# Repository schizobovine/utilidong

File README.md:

utilidong
=============================

Various utility dongles that have uses in many projects:

* USB-to-UART adapter based on the FTDI FT231XS
* Lithium polymer USB battery charger based on the Microchip MCP73831
* DC-to-DC SEPIC converter based on the Linear LT1610

Yes, all of these are available elsewhere for cheaper, on platforms that have had better testing, etc. Don't use them for anything you care about, really, since this is more CAD practice for myself.

Eventually will be a single unit for handling power and UART communications with a microcontroller.

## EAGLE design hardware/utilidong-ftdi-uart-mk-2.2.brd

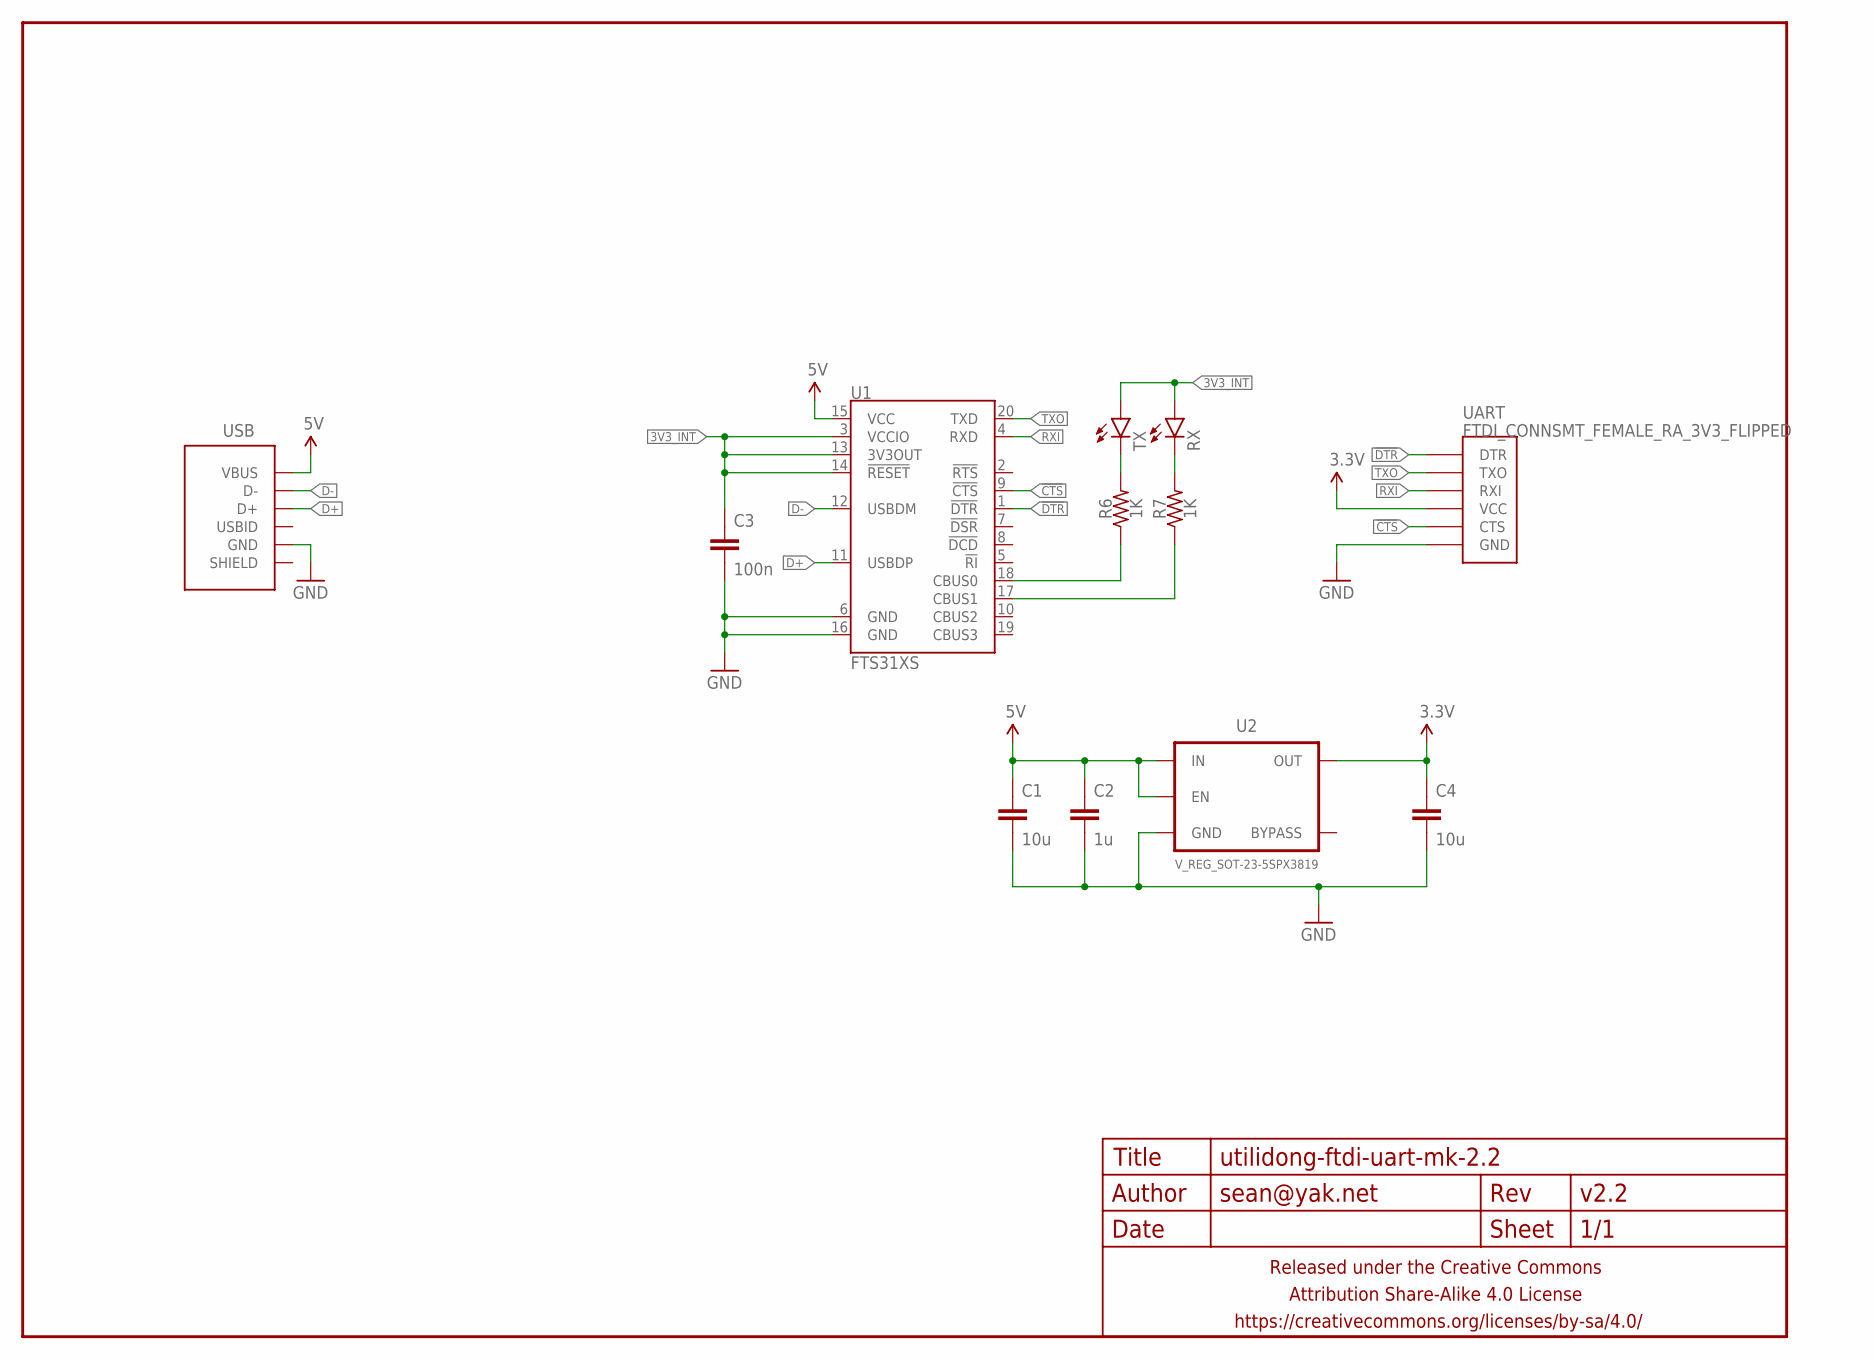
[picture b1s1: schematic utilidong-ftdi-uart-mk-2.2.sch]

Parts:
C1, C4: 10u; C0805
C2: 1u; C0603-TIGHTER
C3: 100n; C0603-TIGHTER
FRAME1: FRAME-LETTERNO_PACKAGE; DUMMY
R6, R7: 1K; R0603-TIGHTER
RX: LED0603-TIGHT; LED-0603-TIGHT
TX: LED0603-TIGHT; LED-0603-TIGHT
U1: FTS31XS; SSOP20_L
U2: V_REG_SOT-23-5SPX3819; SOT23-5
UART: FTDI_CONNSMT_FEMALE_RA_3V3_FLIPPED; FTDI_CONN_SMT_FEMALE_RA_3V3_FLIPPED
USB: USB-AB-SHIELDFCI-10103594-USB-MICRO-B-EVENLESS; FCI-101035840-USB-MICRO-B-EVENLESS

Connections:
3.3V: C4.1, U2.5 (OUT), UART.4 (VCC)
3V3_INT: C3.1, RX.A, TX.A, U1.3 (VCCIO), U1.13 (3V3OUT), U1.14 (!RESET)
5V: C1.1, C2.1, U1.15 (VCC), U2.1 (IN), U2.3 (EN), USB.1 (VBUS)
!CTS: U1.9 (!CTS), UART.5 (CTS)
!DTR: U1.1 (!DTR), UART.1 (DTR)
D+: U1.11 (USBDP), USB.3 (D+)
D-: U1.12 (USBDM), USB.2 (D-)
GND: C1.2, C2.2, C3.2, C4.2, U1.6 (GND), U1.16 (GND), U2.2 (GND), UART.6 (GND), USB.5 (GND)
unnamed: R6.1, U1.18 (CBUS0)
unnamed: R6.2, TX.C
unnamed: R7.2, RX.C
unnamed: R7.1, U1.17 (CBUS1)
RXI: U1.4 (RXD), UART.3 (RXI)
TXO: U1.20 (TXD), UART.2 (TXO)

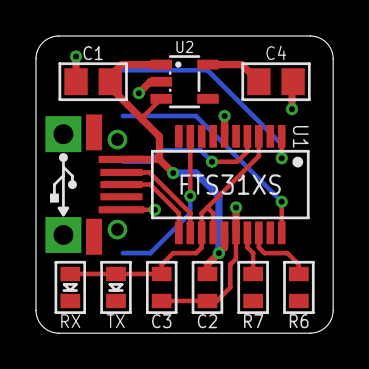
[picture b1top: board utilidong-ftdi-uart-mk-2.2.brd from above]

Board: 2 copper layers, 16.5 x 16.5 mm, 13 parts (1 on the bottom side), 14 nets.

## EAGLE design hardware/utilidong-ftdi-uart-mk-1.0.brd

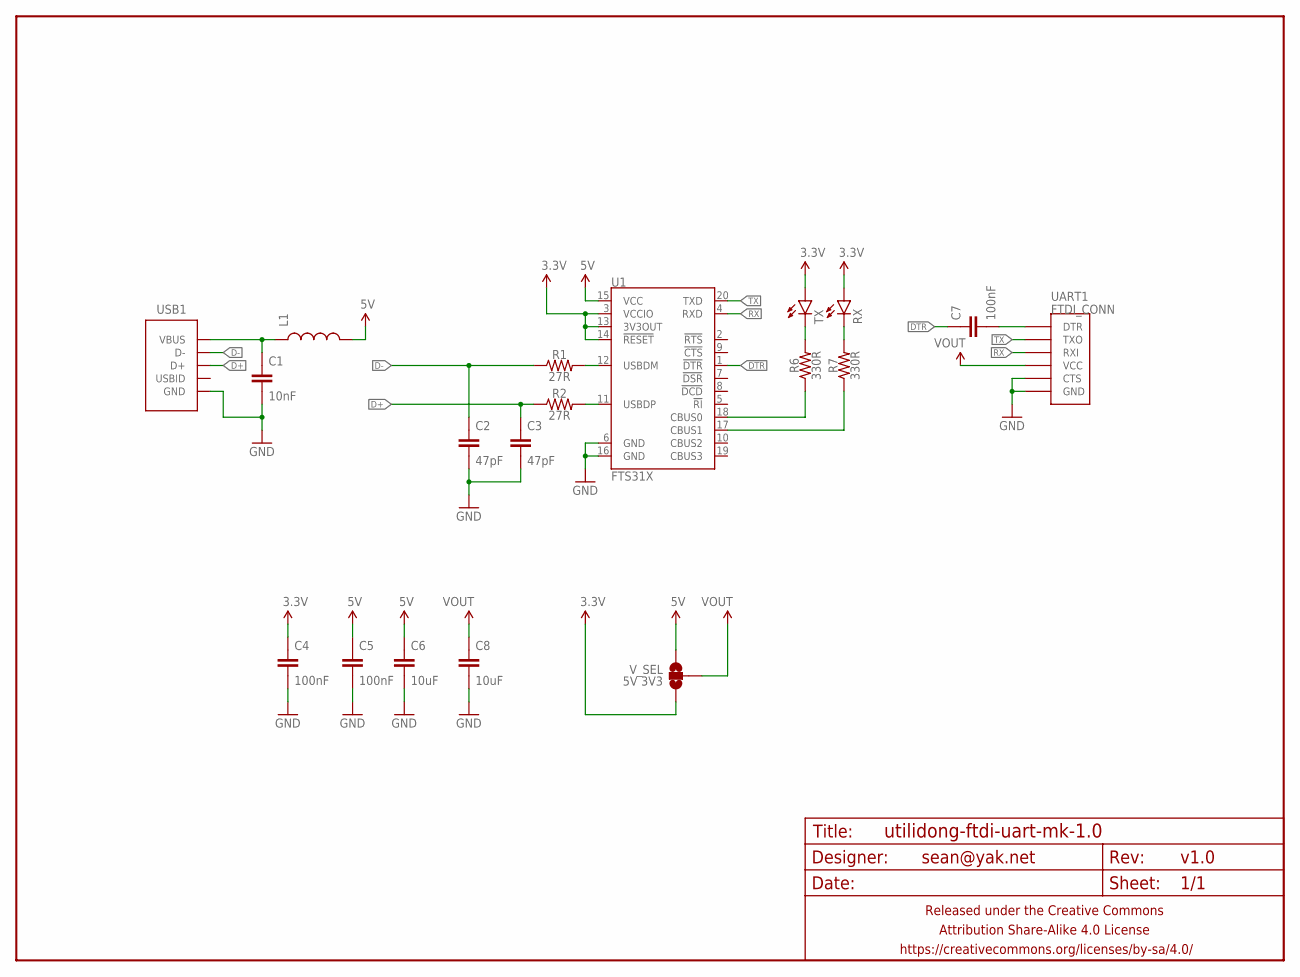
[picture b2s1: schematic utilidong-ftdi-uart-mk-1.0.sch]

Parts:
C1: 10nF; C0805
C2, C3: 47pF; C0805
C4, C5, C7: 100nF; C0805
C6, C8: 10uF; C1206
FRAME1: FRAME-LETTERNO_PACKAGE; DUMMY
L1: INDUCTORL0805; L0805
R1, R2: 27R; R0805
R6, R7: 330R; R0805
RX: LED1206; LED-1206
TX: LED1206; LED-1206
U1: FTS31X; SSOP20_L
UART1: FTDI_CONN
USB1: USB-ABCOMBO; USB-MICRO-B-FCI-CUTOUT
V_SEL: 5V 3V3; PAD-JUMPER-3-NO_YES_SILK_FULL_BOX

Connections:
3.3V: C4.1, RX.A, TX.A, U1.3 (VCCIO), U1.13 (3V3OUT), U1.14 (!RESET), V_SEL.3
5V: C5.1, C6.1, L1.2, U1.15 (VCC), V_SEL.1
D+: C3.1, R2.1, USB1.3 (D+)
D-: C2.1, R1.1, USB1.2 (D-)
DTR: C7.1, U1.1 (!DTR)
GND: C1.2, C2.2, C3.2, C4.2, C5.2, C6.2, C8.2, U1.6 (GND), U1.16 (GND), UART1.CTS, UART1.GND, USB1.5 (GND), USB1.P$1 (GND), USB1.P$2 (GND)
unnamed: R1.2, U1.12 (USBDM)
unnamed: R2.2, U1.11 (USBDP)
unnamed: C1.1, L1.1, USB1.1 (VBUS)
unnamed: C7.2, UART1.DTR
unnamed: R6.1, U1.18 (CBUS0)
unnamed: R6.2, TX.C
unnamed: R7.2, RX.C
unnamed: R7.1, U1.17 (CBUS1)
RX: U1.4 (RXD), UART1.RXI
TX: U1.20 (TXD), UART1.TXO
VOUT: C8.1, UART1.VCC, V_SEL.2

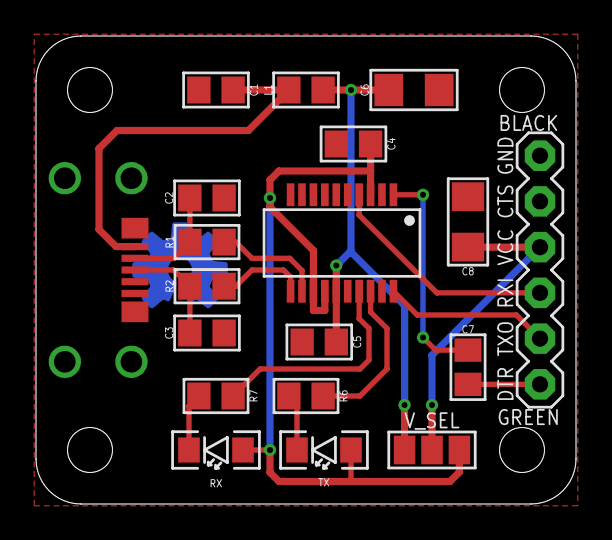
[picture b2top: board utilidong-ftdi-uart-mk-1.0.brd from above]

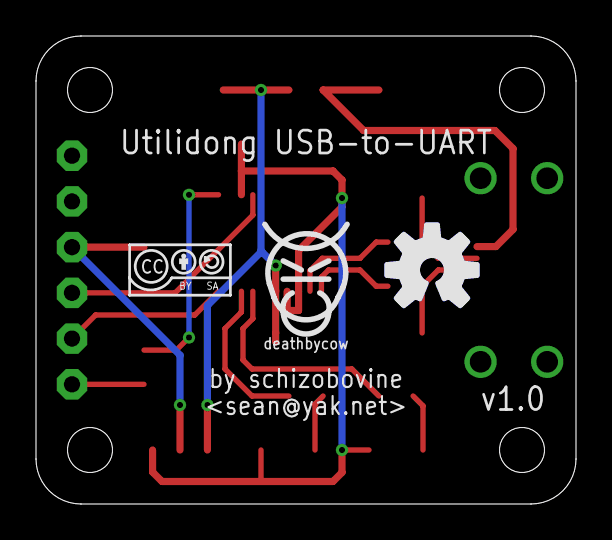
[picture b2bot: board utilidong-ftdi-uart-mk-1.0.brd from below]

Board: 2 copper layers, 30.0 x 26.0 mm, 23 parts (3 on the bottom side), 17 nets.

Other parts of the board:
U$3: COW_SMALL
U$4: CC-BY-SA-4.0-NO-URL
U$6: OSHWLOGO_TOP_0.2_A

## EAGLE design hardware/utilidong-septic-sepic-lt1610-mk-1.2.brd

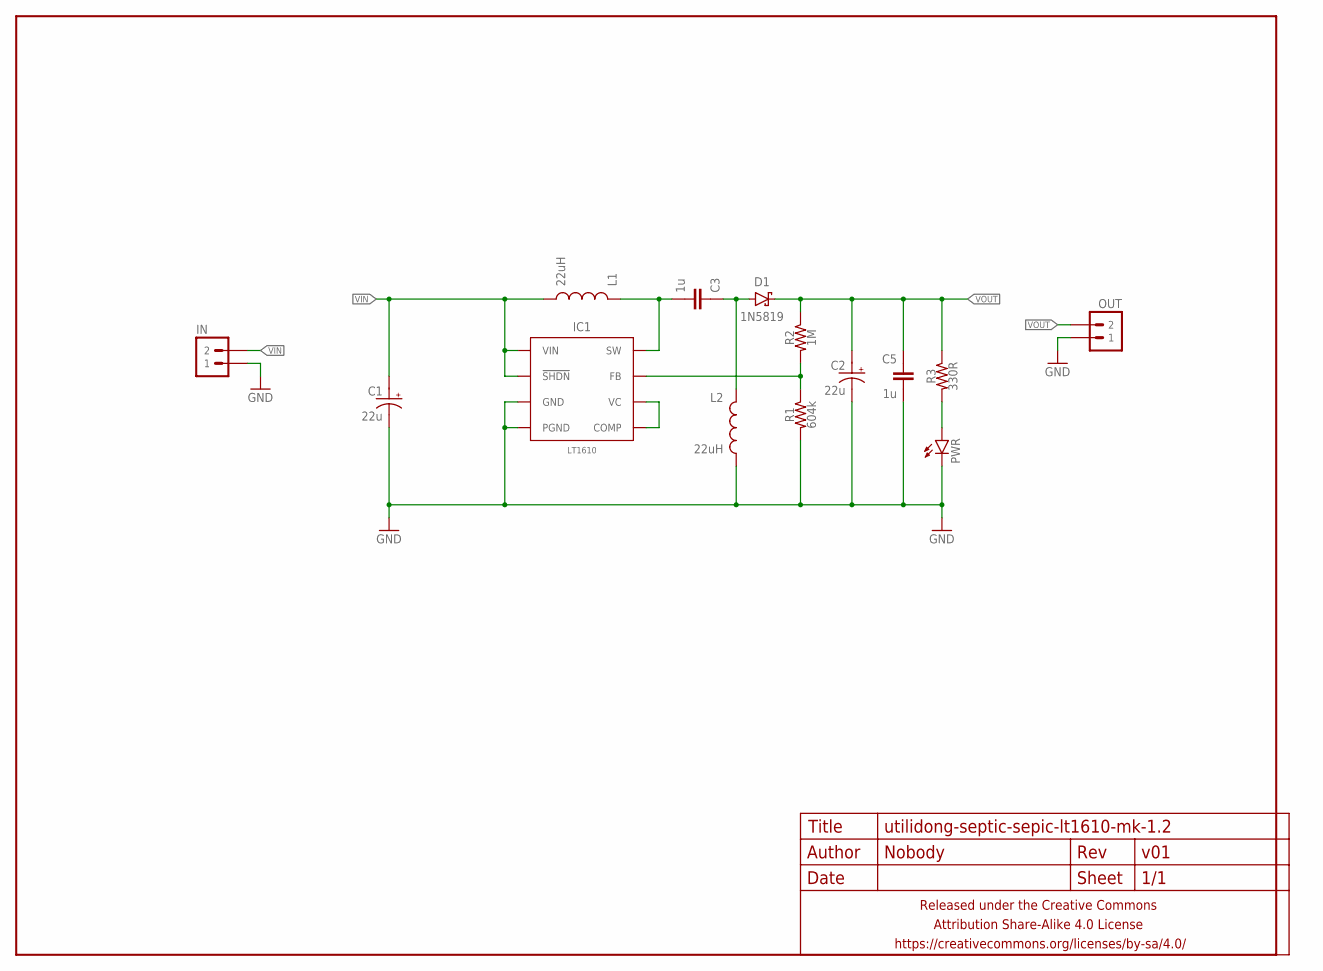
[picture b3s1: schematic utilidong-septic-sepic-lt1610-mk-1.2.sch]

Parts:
C1, C2: 22u; E2,5-6
C3, C5: 1u; C025-024X044
D1: 1N5819; DIODE-7.62MM
FRAME1: FRAME-LETTERNO_PACKAGE; DUMMY
IC1: LT1610; SO08
IN: M02PTH-CENTERED-R+; 1X02-CENTER-R+
L1, L2: 22uH; MURATA-1100R
OUT: M02PTH-CENTERED-R+; 1X02-CENTER-R+
PWR: LED3MM-LESS; LED3MM-LESSSILK
R1: 604k; RESISTOR-AXIAL-PTH-5.08MM
R2: 1M; RESISTOR-AXIAL-PTH-5.08MM
R3: 330R; RESISTOR-AXIAL-PTH-5.08MM

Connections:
GND: C1.-, C2.-, C5.2, IC1.4 (PGND), IC1.7 (GND), IN.1, L2.P$2 (2), OUT.1, PWR.K (C), R1.P$2 (2)
unnamed: PWR.A, R3.P$2 (2)
unnamed: C3.2, IC1.5 (SW), L1.P$1 (1)
unnamed: IC1.1 (VC), IC1.8 (COMP)
unnamed: C3.1, D1.A, L2.P$1 (1)
unnamed: IC1.2 (FB), R1.P$1 (1), R2.P$2 (2)
VIN: C1.+, IC1.3 (!SHDN), IC1.6 (VIN), IN.2, L1.P$2 (2)
VOUT: C2.+, C5.1, D1.K (C), OUT.2, R2.P$1 (1), R3.P$1 (1)

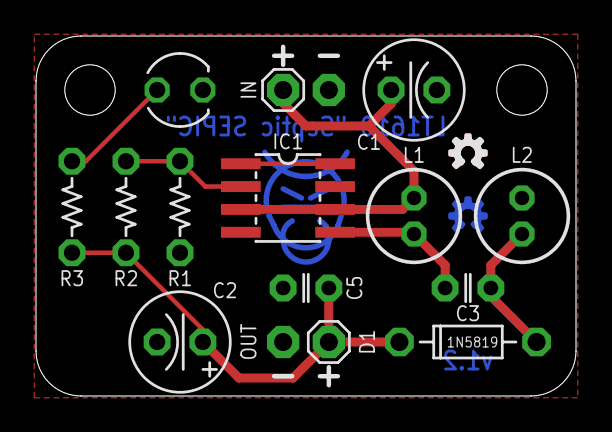
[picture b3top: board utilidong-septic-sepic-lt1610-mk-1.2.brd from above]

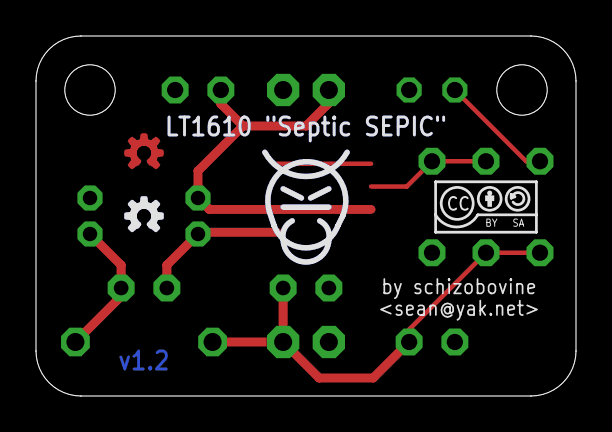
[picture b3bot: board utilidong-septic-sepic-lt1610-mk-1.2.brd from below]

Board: 2 copper layers, 30.0 x 20.0 mm, 19 parts (3 on the bottom side), 8 nets.

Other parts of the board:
U$1: CC-BY-SA-4.0-NO-URL
U$2: COW_SMALL_METAL_NOTEXT
U$3, U$4: OSHWLOGO_MINI

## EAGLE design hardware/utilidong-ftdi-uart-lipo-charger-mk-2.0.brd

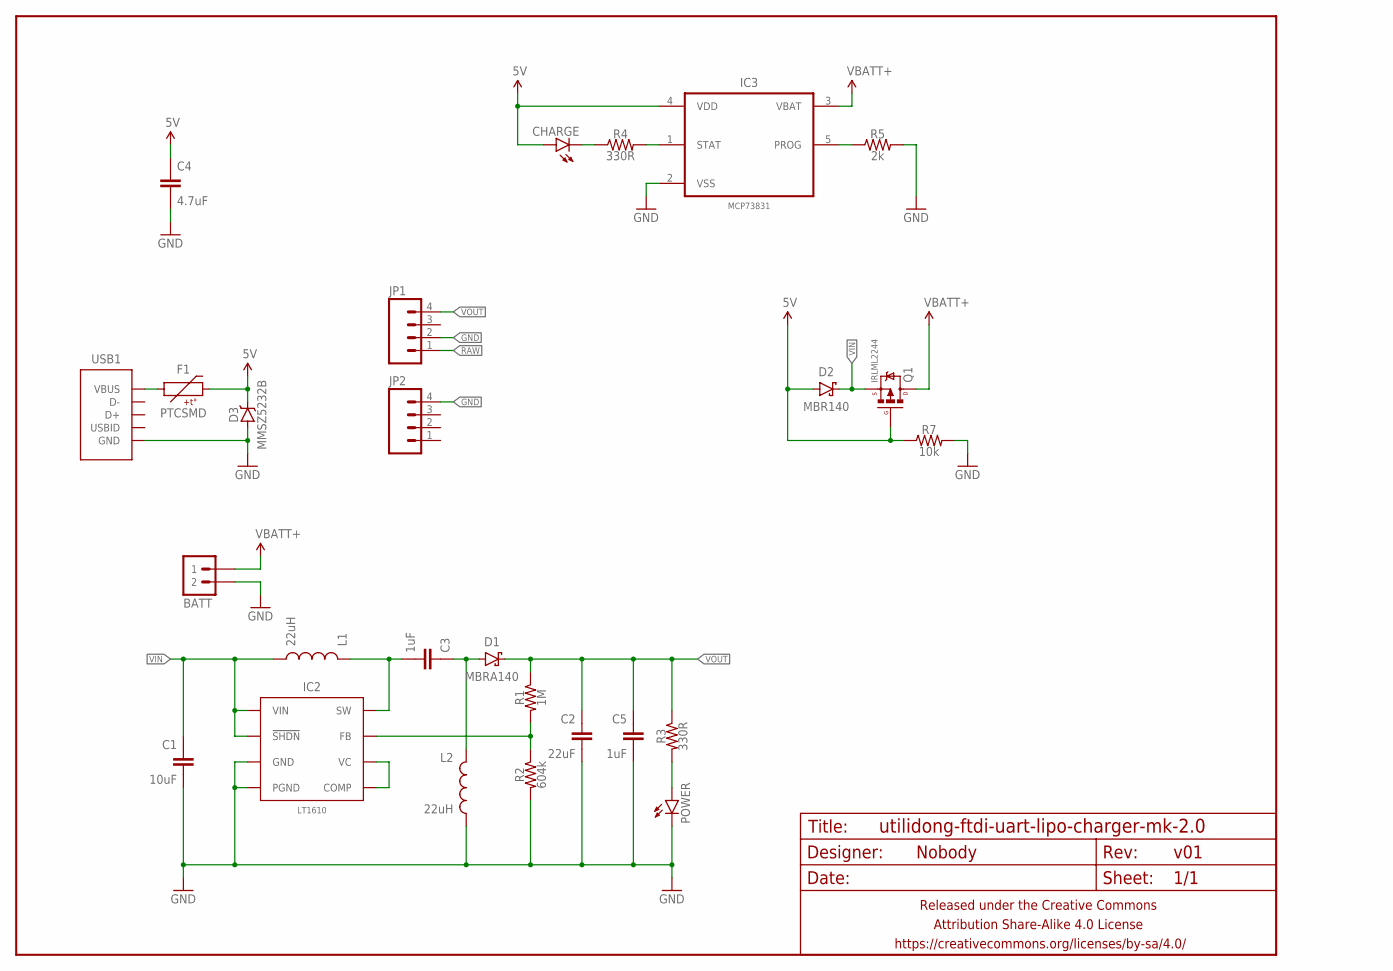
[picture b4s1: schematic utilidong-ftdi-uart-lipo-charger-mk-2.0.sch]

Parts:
BATT: M02JST-2MM-SMT; JST-2-SMD
C1: 10uF; C0805
C2: 22uF; C1206
C3, C5: 1uF; C0805
C4: 4.7uF; C0603
CHARGE: LED1206; LED-1206
D1: MBRA140; SOD123-SCHOTTKY
D2: MBR140; SOD123-SCHOTTKY
D3: MMSZ5232B; SOD123-ZENER
F1: PTCSMD; PTC-1206
FRAME1: FRAME-LETTERNO_PACKAGE; DUMMY
IC2: LT1610; SO08
IC3: MCP73831; SOT95P280X145-5N
JP1, JP2: M04PTH; 1X04-PTH-VERT
L1, L2: 22uH; TAIYO-YUDEN-40XX
POWER: LED1206; LED-1206
Q1: IRLML2244; SOT23-3
R1: 1M; R0603
R2: 604k; R0603
R3, R4: 330R; R0603
R5: 2k; R0603
R7: 10k; R0603
USB1: USB-ABCOMBO; USB-MICRO-B-FCI-CUTOUT

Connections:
5V: C4.1, CHARGE.A, D2.A, D3.C, F1.2, IC3.4 (VDD), Q1.1 (G), R7.1
GND: BATT.1 (2), C1.2, C2.2, C4.2, C5.2, D3.A, IC2.4 (PGND), IC2.7 (GND), IC3.2 (VSS), JP1.2, JP2.4, L2.2, POWER.C, R2.2, R5.2, R7.2, USB1.5 (GND), USB1.P$1 (GND), USB1.P$2 (GND)
unnamed: POWER.A, R3.2
unnamed: C3.2, IC2.5 (SW), L1.1
unnamed: IC3.1 (STAT), R4.2
unnamed: IC2.1 (VC), IC2.8 (COMP)
unnamed: C3.1, D1.A, L2.1
unnamed: CHARGE.C, R4.1
unnamed: IC2.2 (FB), R1.2, R2.1
unnamed: IC3.5 (PROG), R5.1
unnamed: F1.1, USB1.1 (VBUS)
RAW: JP1.1
VBATT+: BATT.2 (1), IC3.3 (VBAT), Q1.3 (D)
VIN: C1.1, D2.C, IC2.3 (!SHDN), IC2.6 (VIN), L1.2, Q1.2 (S)
VOUT: C2.1, C5.1, D1.C, JP1.4, R1.1, R3.1

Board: 2 copper layers, 27 parts (2 on the bottom side), 14 nets, no tracks yet.

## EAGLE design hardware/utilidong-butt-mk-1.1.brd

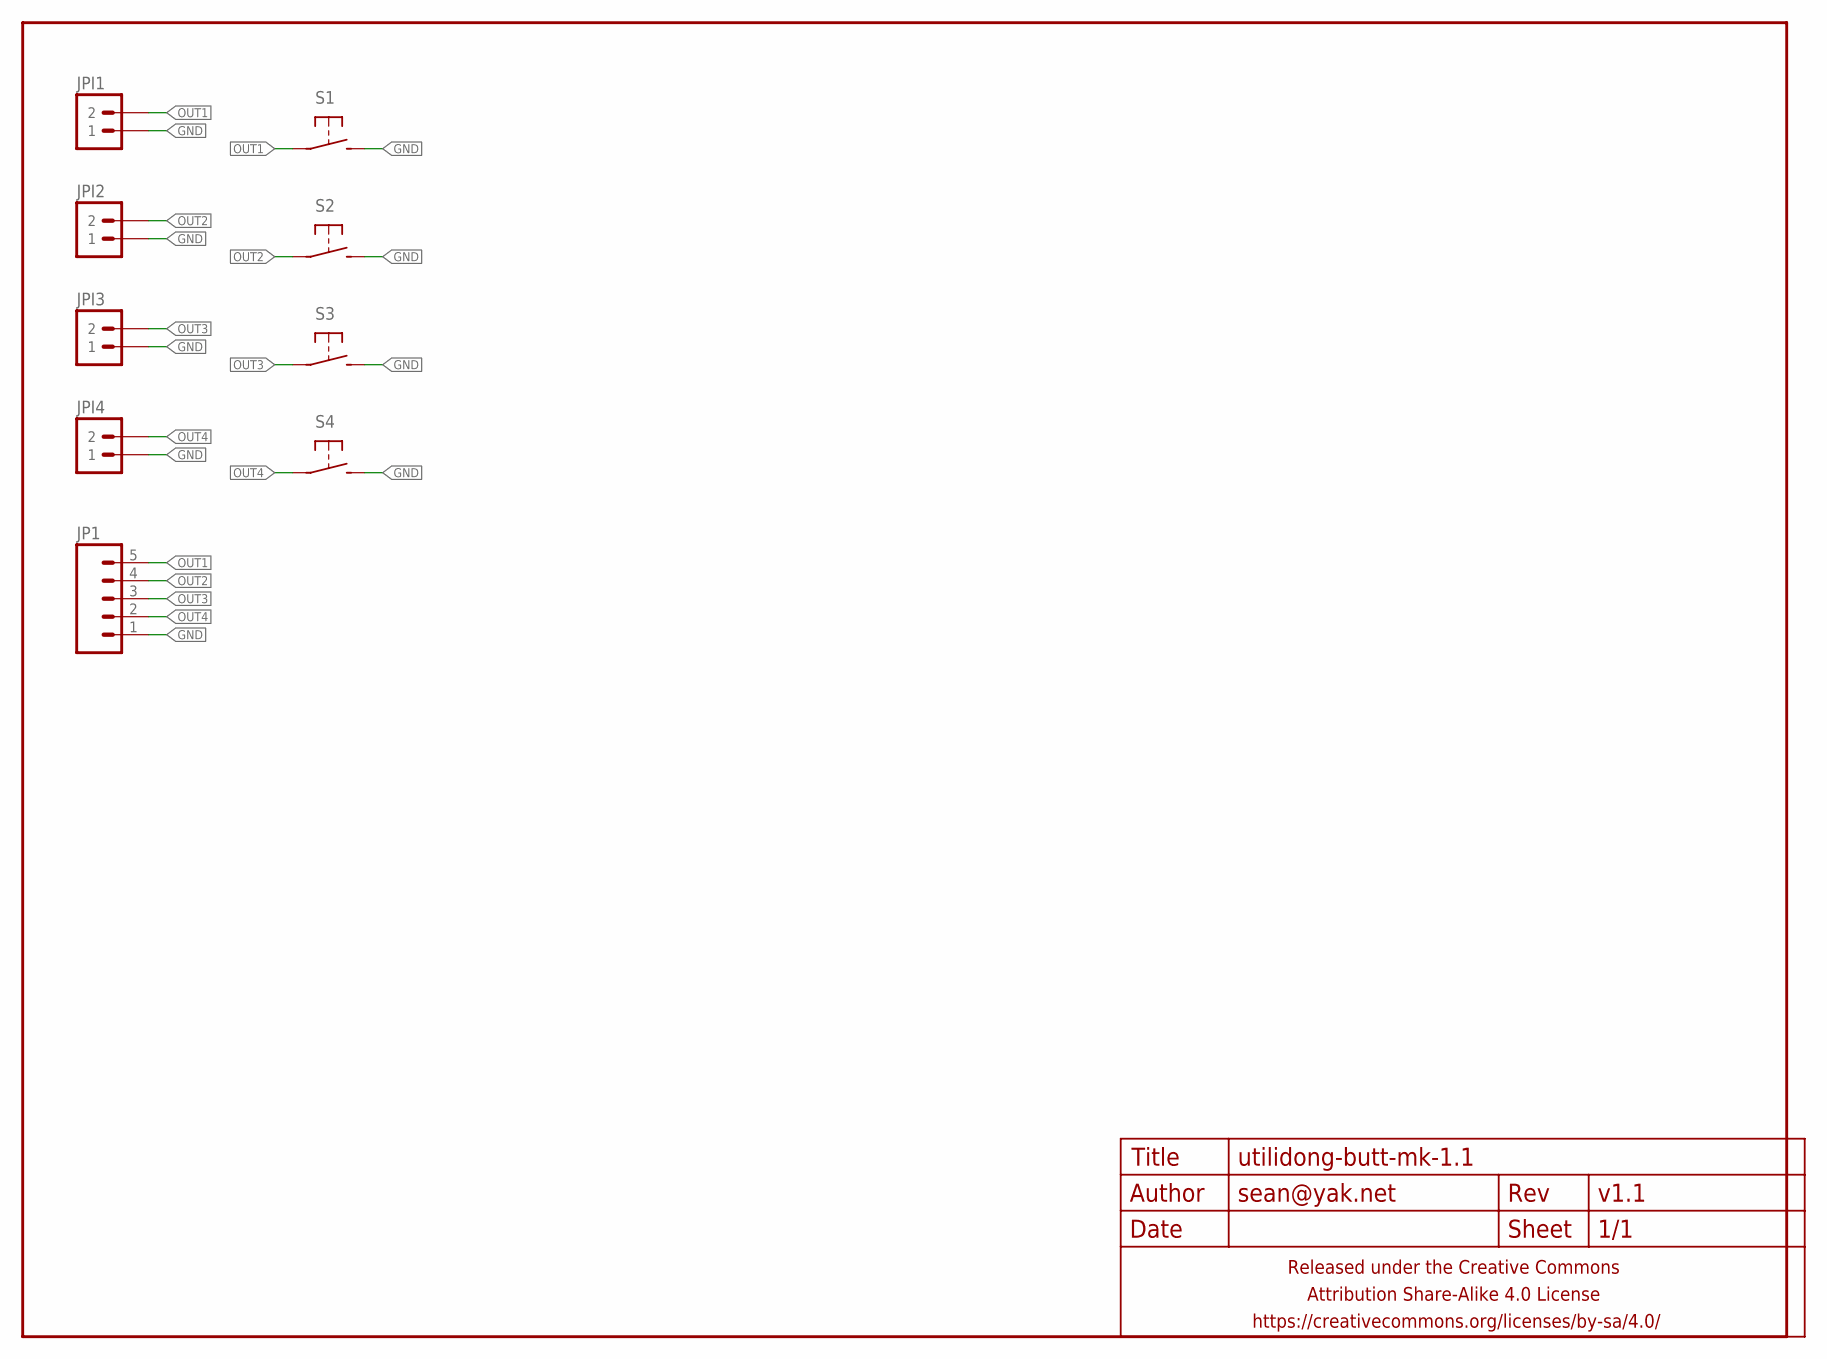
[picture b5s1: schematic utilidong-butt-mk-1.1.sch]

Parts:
FRAME1: FRAME-LETTERNO_PACKAGE; DUMMY
JP1: M05JST-PH-VERT-PTH; JST-5-PH-VERT-PTH
JPI1, JPI2, JPI3, JPI4: M02PTH-CENTERED; 1X02-CENTER
S1, S2, S3, S4: SPST-NO-TACT6MM-PTH-SMALL-PADS; DTS-6-SMALL-PADS

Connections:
GND: JP1.1, JPI1.1, JPI2.1, JPI3.1, JPI4.1, S1.3 (2), S1.4 (2), S2.3 (2), S2.4 (2), S3.3 (2), S3.4 (2), S4.3 (2), S4.4 (2)
OUT1: JP1.5, JPI1.2, S1.1, S1.2 (1)
OUT2: JP1.4, JPI2.2, S2.1, S2.2 (1)
OUT3: JP1.3, JPI3.2, S3.1, S3.2 (1)
OUT4: JP1.2, JPI4.2, S4.1, S4.2 (1)

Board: 2 copper layers, 10 parts (0 on the bottom side), 5 nets, no tracks yet.

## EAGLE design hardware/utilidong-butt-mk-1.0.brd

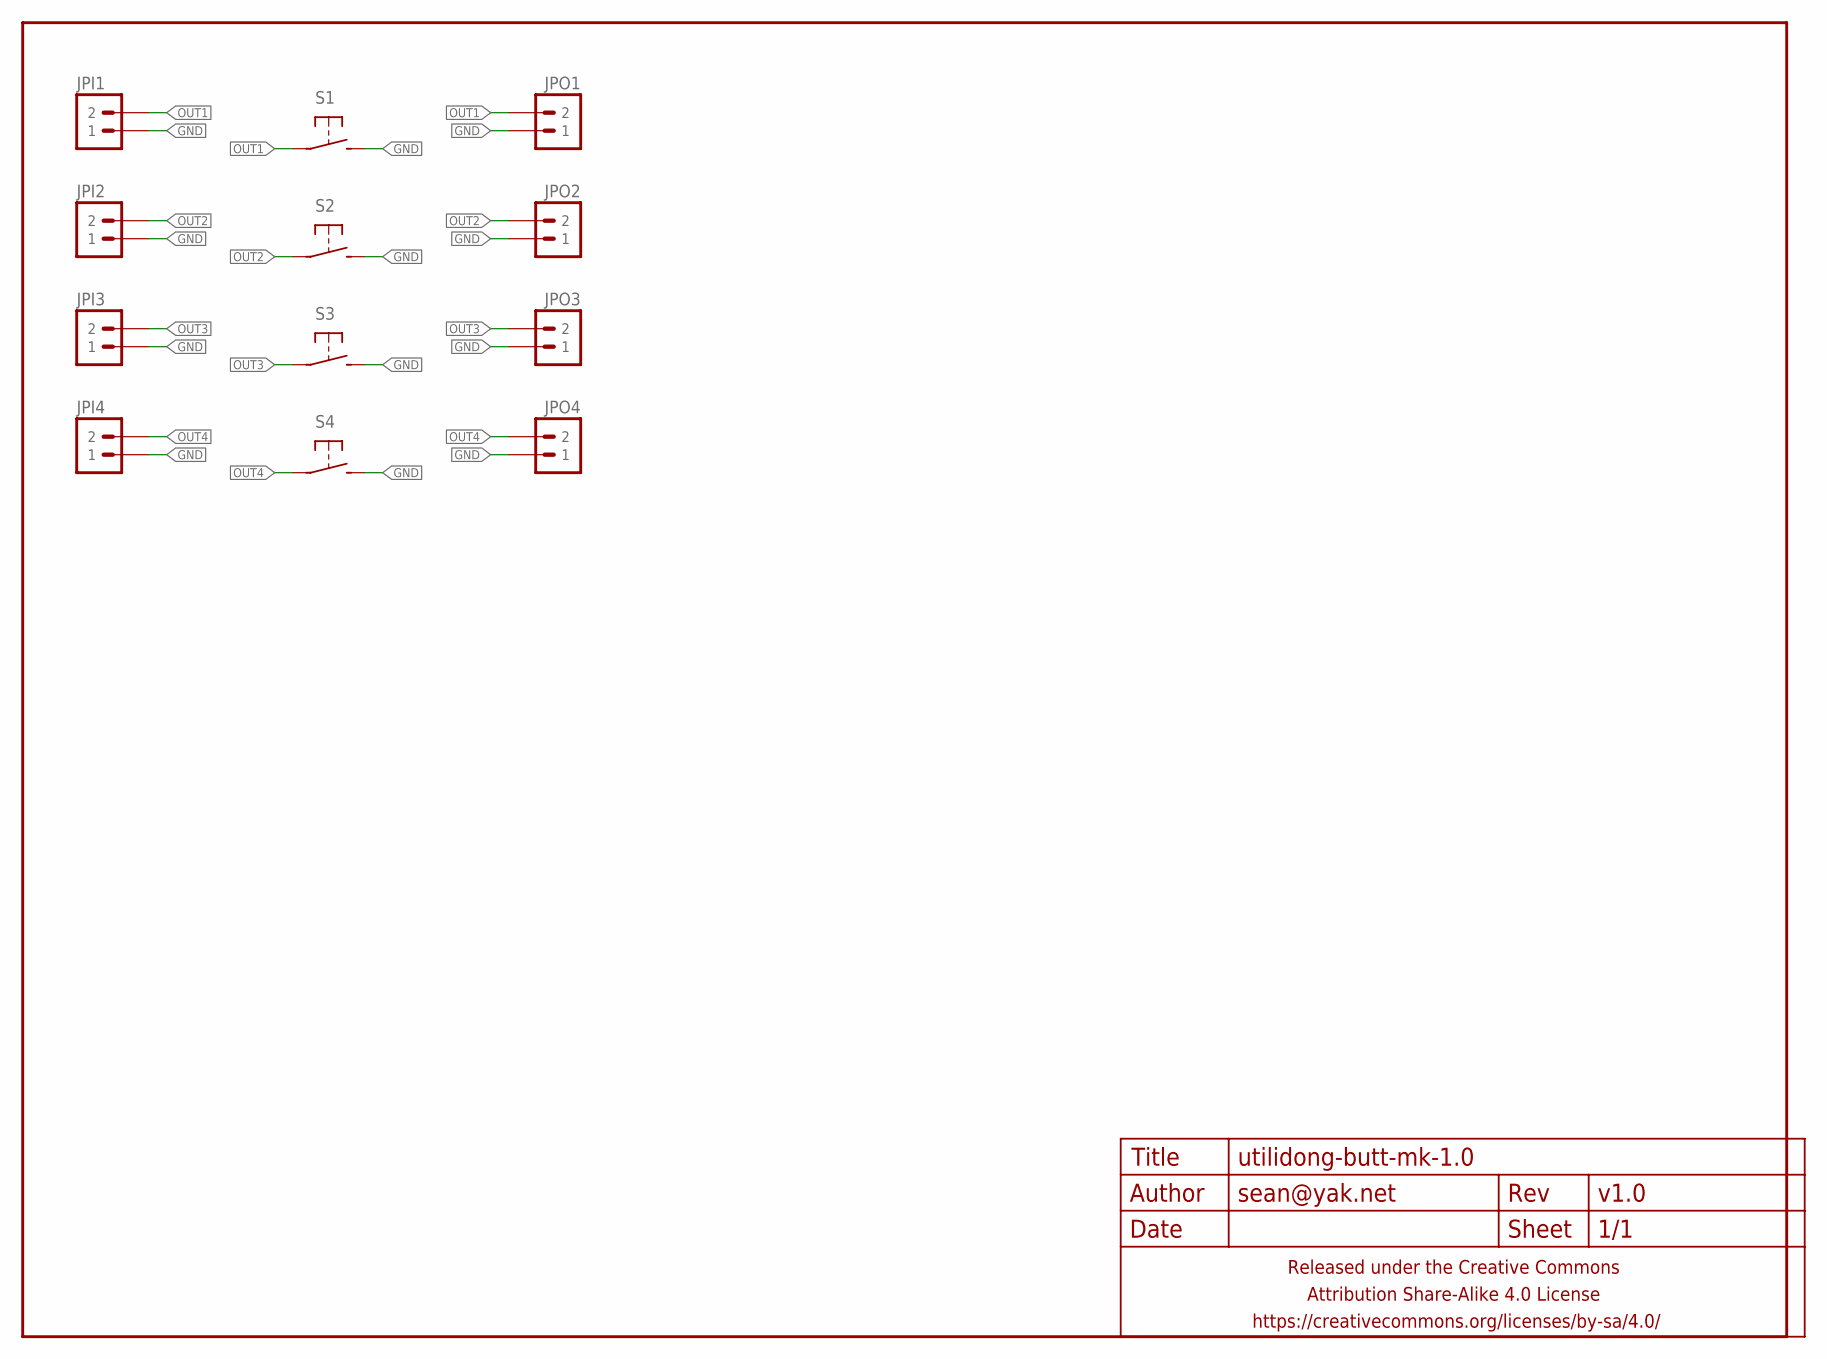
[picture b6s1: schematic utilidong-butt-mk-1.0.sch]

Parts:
FRAME1: FRAME-LETTERNO_PACKAGE; DUMMY
JPI1, JPI2, JPI3, JPI4: M02PTH-CENTERED; 1X02-CENTER
JPO1, JPO2, JPO3, JPO4: M02PTH-CENTERED; 1X02-CENTER
S1, S2, S3, S4: SPST-NO-TACT6MM-PTH-SMALL-PADS; DTS-6-SMALL-PADS

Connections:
GND: JPI1.1, JPI2.1, JPI3.1, JPI4.1, JPO1.1, JPO2.1, JPO3.1, JPO4.1, S1.3 (2), S1.4 (2), S2.3 (2), S2.4 (2), S3.3 (2), S3.4 (2), S4.3 (2), S4.4 (2)
OUT1: JPI1.2, JPO1.2, S1.1, S1.2 (1)
OUT2: JPI2.2, JPO2.2, S2.1, S2.2 (1)
OUT3: JPI3.2, JPO3.2, S3.1, S3.2 (1)
OUT4: JPI4.2, JPO4.2, S4.1, S4.2 (1)

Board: 2 copper layers, 13 parts (0 on the bottom side), 5 nets, no tracks yet.

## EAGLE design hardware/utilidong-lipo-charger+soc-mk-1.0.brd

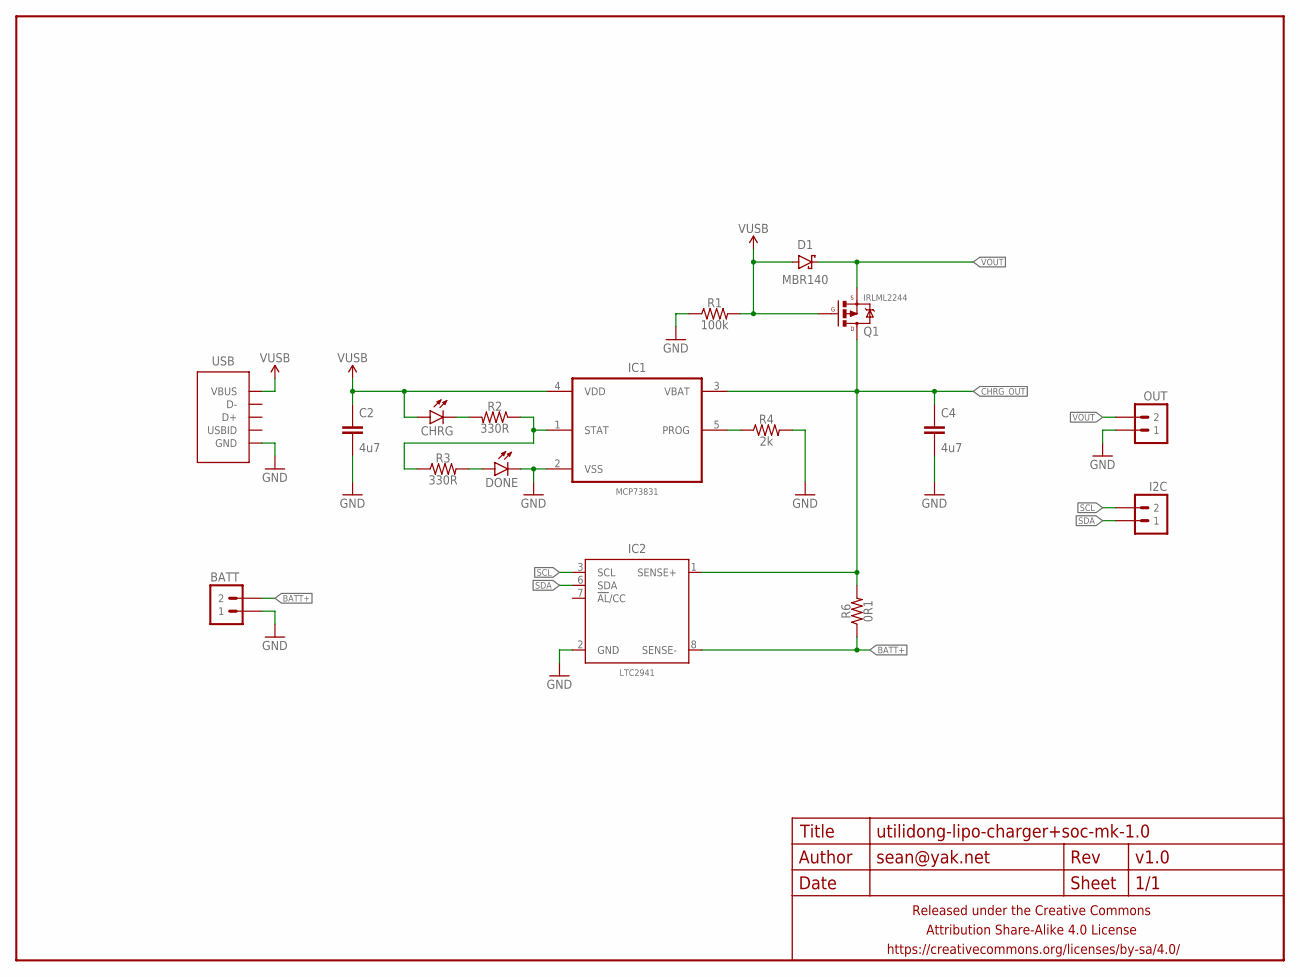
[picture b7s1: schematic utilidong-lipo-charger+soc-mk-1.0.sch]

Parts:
BATT: M02PTH-CENTERED-R+; 1X02-CENTER-R+
C2, C4: 4u7; C0603
CHRG: LED0603; LED-0603
D1: MBR140; SOD123-SCHOTTKY
DONE: LED0603; LED-0603
FRAME1: FRAME-LETTERNO_PACKAGE; DUMMY
I2C: M02PTH; 1X02
IC1: MCP73831; SOT95P280X145-5N
IC2: LTC2941; MSOP-8
OUT: M02PTH-CENTERED-R+; 1X02-CENTER-R+
Q1: IRLML2244; SOT23-3
R1: 100k; R0603
R2, R3: 330R; R0603
R4: 2k; R0603
R6: 0R1; R0603
USB: USB-ABFCI-10103594-USB-MICRO-B-LESS; FCI-10103594-USB-MICRO-B-LESS

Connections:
BATT+: BATT.2, IC2.8 (SENSE-), R6.1
CHRG_OUT: C4.1, IC1.3 (VBAT), IC2.1 (SENSE+), Q1.3 (D), R6.2
GND: BATT.1, C2.2, C4.2, DONE.C, IC1.2 (VSS), IC2.2 (GND), OUT.1, R1.1, R4.2, USB.5 (GND)
unnamed: CHRG.C, R2.2
unnamed: DONE.A, R3.2
unnamed: IC1.1 (STAT), R2.1, R3.1
unnamed: IC1.5 (PROG), R4.1
SCL: I2C.2, IC2.3 (SCL)
SDA: I2C.1, IC2.6 (SDA)
VOUT: D1.C, OUT.2, Q1.2 (S)
VUSB: C2.1, CHRG.A, D1.A, IC1.4 (VDD), Q1.1 (G), R1.2, USB.1 (VBUS)

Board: 2 copper layers, 19 parts (1 on the bottom side), 11 nets, no tracks yet.

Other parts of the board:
U$8: CC-BY-SA-4.0-NO-URL

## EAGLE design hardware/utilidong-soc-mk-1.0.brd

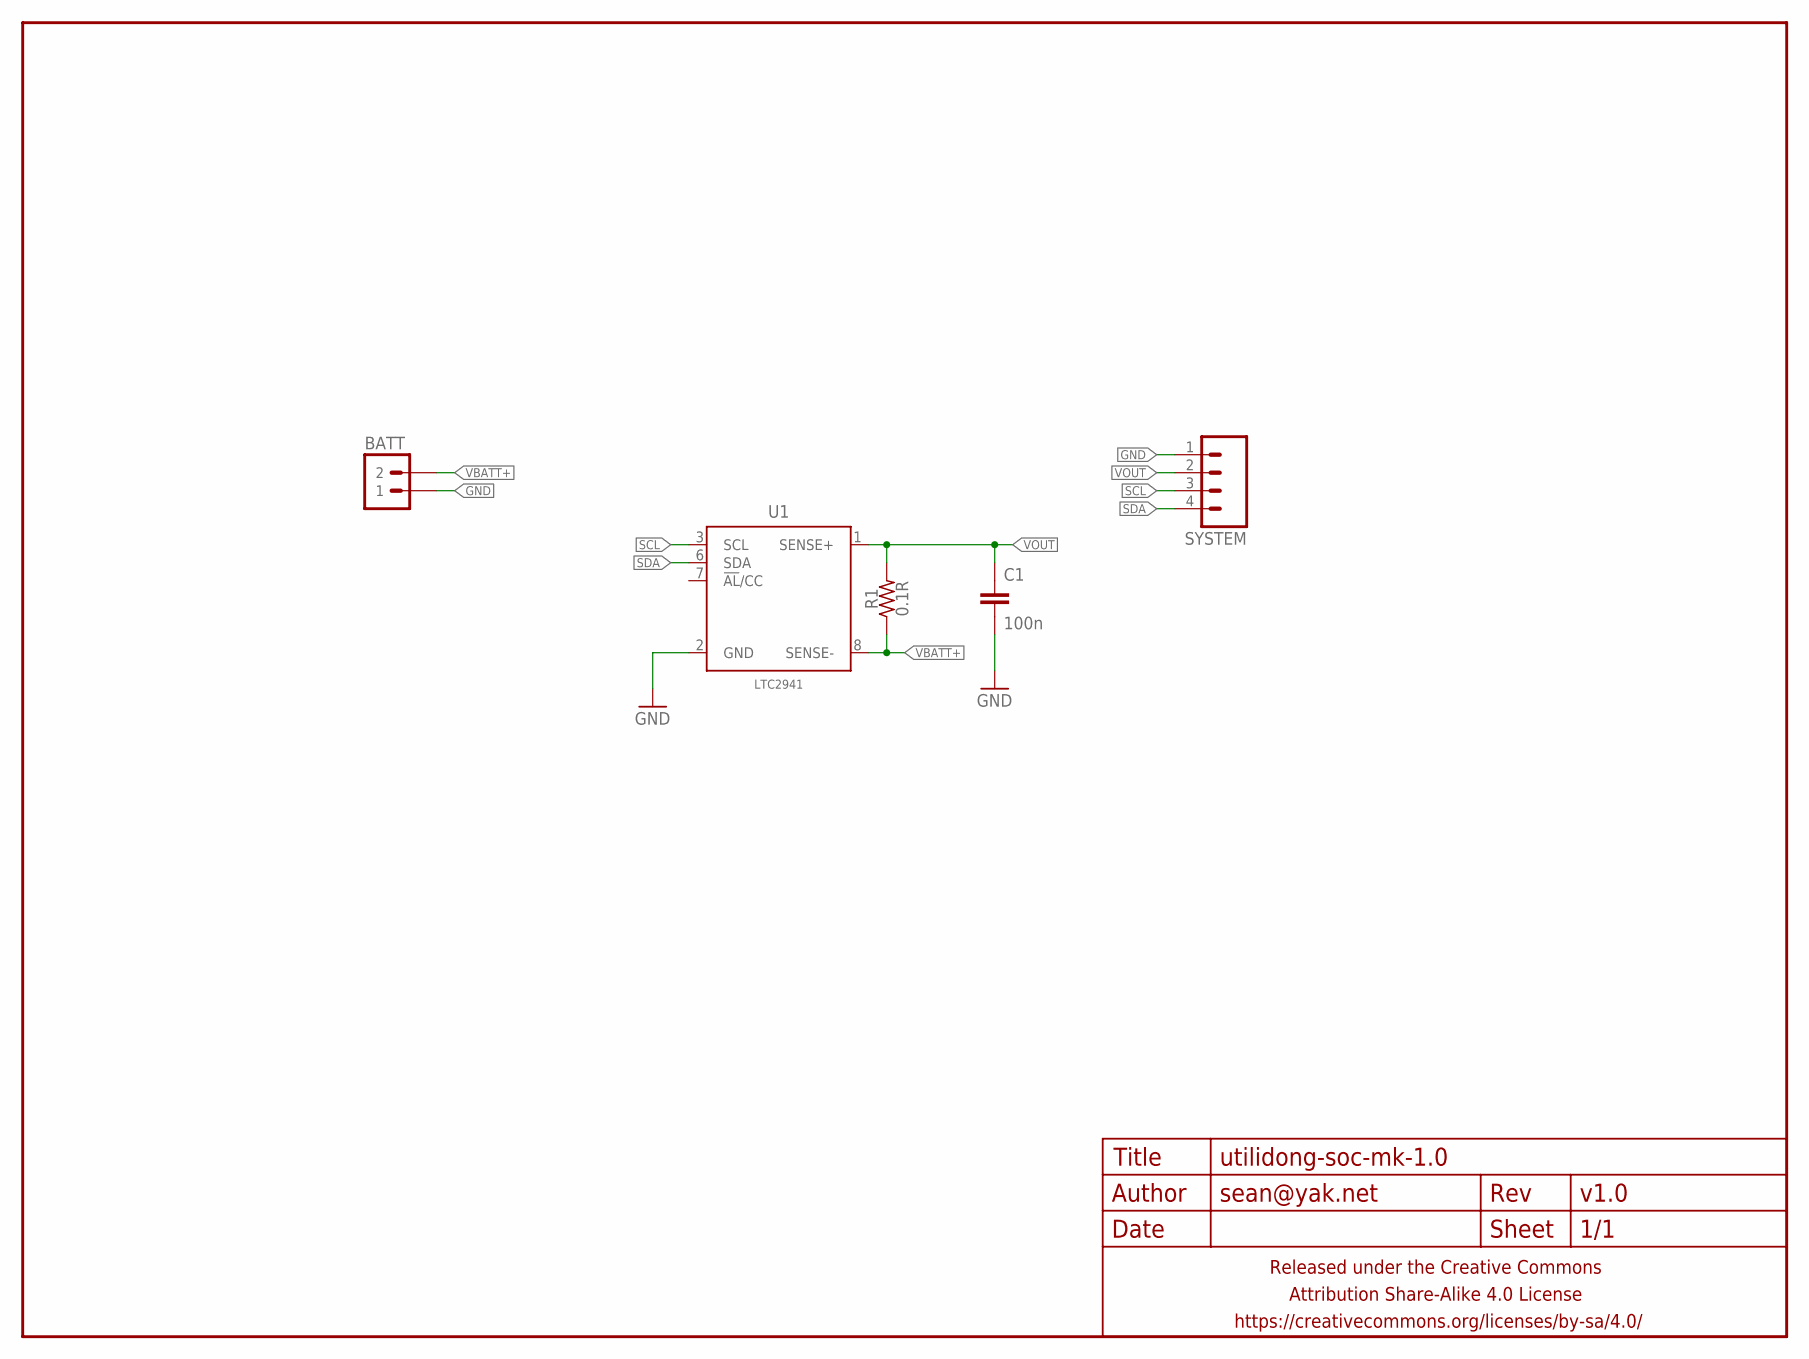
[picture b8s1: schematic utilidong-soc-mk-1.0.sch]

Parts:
BATT: M02PTH-CENTERED-R+; 1X02-CENTER-R+
C1: 100n; C0603
FRAME1: FRAME-LETTERNO_PACKAGE; DUMMY
R1: 0.1R; R1206
SYSTEM: M04PTH-CENTERED; 1X04-PTH-VERT-CENTER
U1: LTC2941; MSOP-8

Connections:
GND: BATT.1, C1.2, SYSTEM.1, U1.2 (GND)
SCL: SYSTEM.3, U1.3 (SCL)
SDA: SYSTEM.4, U1.6 (SDA)
VBATT+: BATT.2, R1.1, U1.8 (SENSE-)
VOUT: C1.1, R1.2, SYSTEM.2, U1.1 (SENSE+)

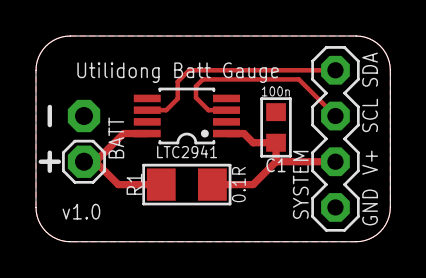
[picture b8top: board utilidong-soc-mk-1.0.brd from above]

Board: 2 copper layers, 19.7 x 11.4 mm, 7 parts (1 on the bottom side), 5 nets.

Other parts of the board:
U$1: COW_SMALL_NOTEXT

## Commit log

2015-06-09 initial commit of current boards
2015-06-15 testing p-mosfet plus diode for automatic power sharing
2015-06-15 sepic power supply copied from switcharoo repo to here for integration
2015-06-15 that shouldn't be here
2015-06-15 first version combining psu and charger
2015-06-15 stand-alone usb lipo charger
2015-06-17 new version of lipo charger with system load balancing
2015-06-17 switching to 0805 for most everything and finished layout
2015-06-22 even tinier smt lipo prototype
2015-06-22 twiddling around
2016-08-03 various fresh, new attempts at not sucking at this
2016-08-03 new obsession with coulomb counters
2016-08-03 i make butt joke funny haha sorry
2016-08-03 i suck at this
2016-08-03 alkdfjkaldsfja
2016-08-03 almost finished way smaller form factor, now flipped to the correct orientation

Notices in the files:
parts and their libraries:
A_butts: Released under the Creative Commons Attribution Share-Alike 4.0 License
A_butts: https://creativecommons.org/licenses/by-sa/4.0
A_butts: Released under the Creative Commons
